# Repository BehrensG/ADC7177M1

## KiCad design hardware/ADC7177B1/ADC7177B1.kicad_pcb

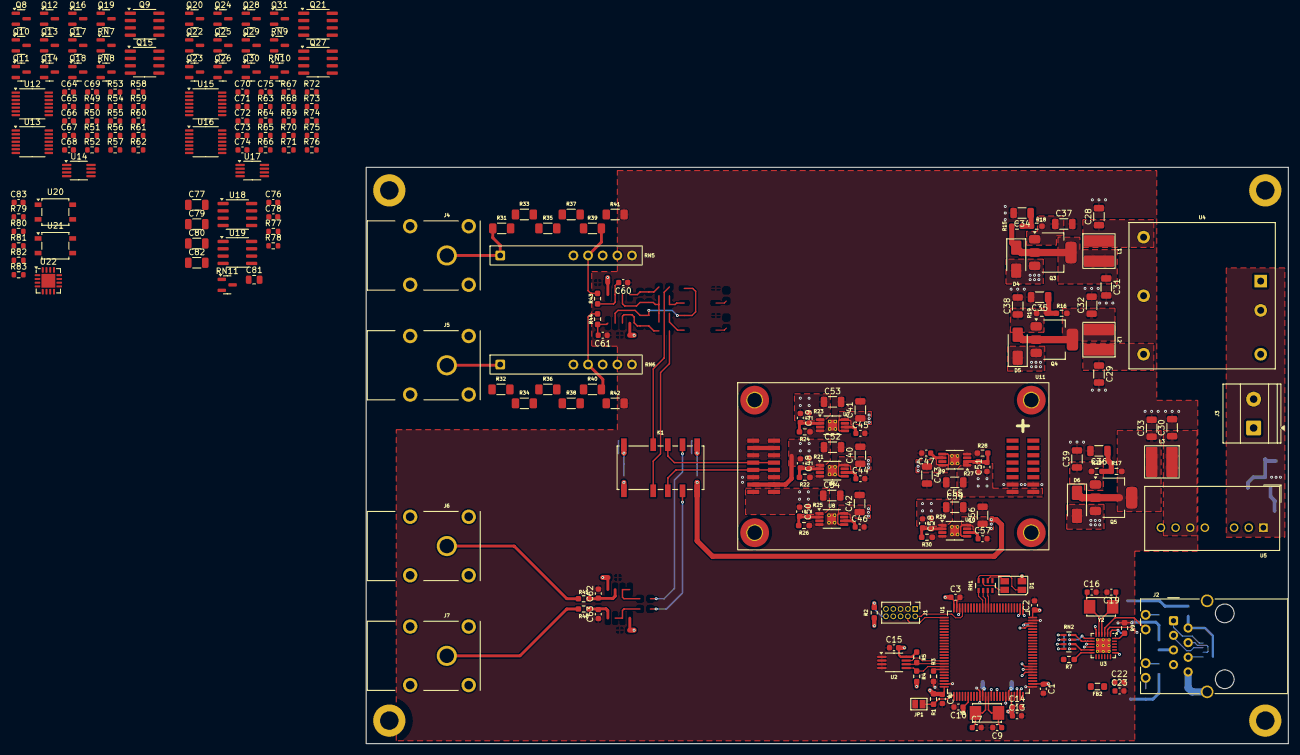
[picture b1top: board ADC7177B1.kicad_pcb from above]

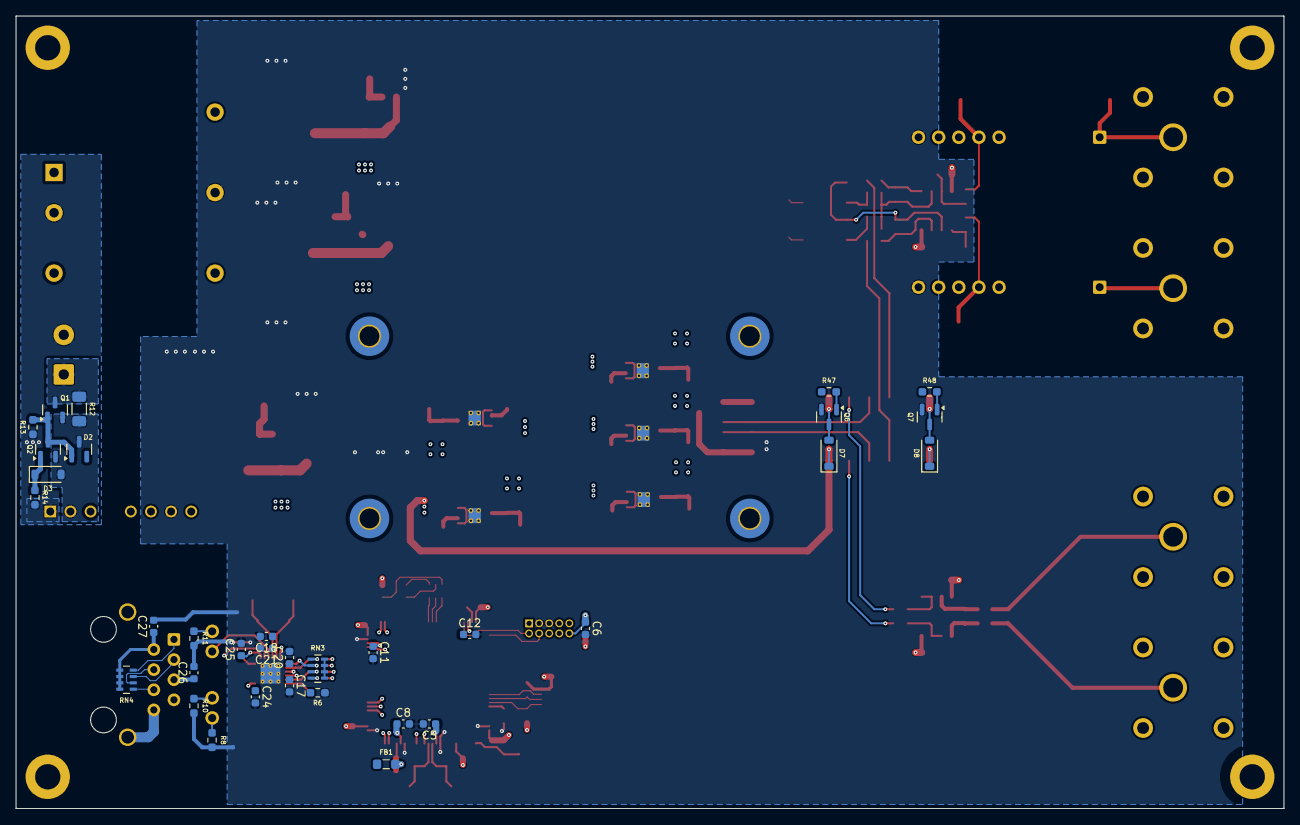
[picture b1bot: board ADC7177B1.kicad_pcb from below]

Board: 4 copper layers, 160.0 x 100.0 mm, 262 parts (33 on the bottom side), 178 nets.

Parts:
C1, C2, C3, C4, C5, C6, C8, C14, C15, C17, C23, C24, C25, C26, C27, C60, C61, C62, C63, C64, C65, C66, C67, C68, C69, C70, C71, C72, C73, C74, C75, C76, C78: 0.1u; C_0603_1608Metric
C7, C9, C16, C19: 8p; C_0603_1608Metric
C10, C20, C21, C22: 1u; C_0603_1608Metric
C11, C12: 2u2; C_0603_1608Metric
C13: 10u; C_0603_1608Metric
C18: 470p; C_0603_1608Metric
C28, C29, C30, C31, C32, C33, C34, C35, C36, C37, C38, C39, C40, C41, C42, C43, C52, C53, C54, C55, C56, C59: 10u/50V; C_1206_3216Metric
C44, C45, C46, C47, C48, C49, C50, C51, C57, C58: 10n; C_0603_1608Metric
C77, C79, C80, C82: 10u; C_1206_3216Metric
C81: 2u2; C_0805_2012Metric
C83: 100p; C_0603_1608Metric
D1: ASMB-MTB1-0B3A2; LED_Avago_PLCC4_3.2x2.8mm_CW
D2: BZX84C10LT1G; SOT-23
D3, D7, D8: 1N4148W; D_SOD-123
D4, D5, D6: SS16; D_SMA
FB1, FB2: 742792031; L_0805_2012Metric_Pad1.05x1.20mm_HandSolder
H1, H2, H3, H4: MountingHole; MountingHole_3.2mm_M3_DIN965_Pad
H5, H6, H7, H8: MountingHole; MountingHole_2.5mm_Pad_TopBottom
J1: 20021111-00010T4LF; PinHeader_2x05_P1.27mm_Vertical
J2: RJ45_Wuerth_7499010121A; RJ45_Wuerth_7499010121A_Horizontal
J3: 1715721; TerminalBlock_Phoenix_MKDS-1,5-2_1x02_P5.00mm_Horizontal
J4, J5, J6, J7: Conn_01x01; S16N-PC
JP1: Open; SolderJumper-2_P1.3mm_Open_Pad1.0x1.5mm
K1: G6SK-2F-DC5; G6SK-2F
L1, L2, L3: 74408943100
Q1: SI5618A; SOT-23
Q2, Q6, Q7: MMBT3904; SOT-23
Q3, Q5: FZT851; SOT-223
Q4: FZT951; SOT-223
Q8, Q10, Q12, Q13, Q14, Q16, Q18, Q19, Q20, Q22, Q24, Q25, Q26, Q28, Q30, Q31: MMBT6429; SOT-23
Q9, Q15, Q21, Q27: JFE2140D; SOIC-8_3.9x4.9mm_P1.27mm
Q11, Q17, Q23, Q29: MMBF4392; SOT-23
R1, R2, R6, R8, R22, R24, R26, R28, R30, R47, R48: 10k; R_0603_1608Metric_Pad0.98x0.95mm_HandSolder
R3: 0; R_0603_1608Metric_Pad0.98x0.95mm_HandSolder
R4, R5: 4k7; R_0603_1608Metric_Pad0.98x0.95mm_HandSolder
R7: 1k5; R_0603_1608Metric_Pad0.98x0.95mm_HandSolder
R9: 12k1; R_0603_1608Metric_Pad0.98x0.95mm_HandSolder
R10, R11: 560; R_0603_1608Metric_Pad0.98x0.95mm_HandSolder
R12: 0; R_1206_3216Metric_Pad1.30x1.75mm_HandSolder
R13, R14: 100k; R_0603_1608Metric_Pad0.98x0.95mm_HandSolder
R15, R16, R17, R18, R19, R20: 1k; R_0603_1608Metric_Pad0.98x0.95mm_HandSolder
R21, R23, R25, R27, R29: 120k; R_0603_1608Metric_Pad0.98x0.95mm_HandSolder
R31, R32, R33, R34, R35, R36, R37, R38: 2M2/0.05%; R_1206_3216Metric_Pad1.30x1.75mm_HandSolder
R39, R40: 1M1/0.05%; R_1206_3216Metric_Pad1.30x1.75mm_HandSolder
R41, R42: 100k/0.05%; R_1206_3216Metric_Pad1.30x1.75mm_HandSolder
R43, R44, R45, R46: 510; R_0603_1608Metric_Pad0.98x0.95mm_HandSolder
R49, R56, R63, R70: 14k7; R_0603_1608Metric
R50, R51, R55, R57, R58, R62, R64, R65, R69, R71, R72, R76: 21k5/0.125W; R_0603_1608Metric
R52, R53, R54, R59, R60, R61, R66, R67, R68, R73, R74, R75: 2k/0.1%; R_0603_1608Metric
R77, R78: 10k/0.01%/2ppm; R_0603_1608Metric
R79, R80: 1k; R_0603_1608Metric
R81: 5k49/0.1%/10ppm; R_0603_1608Metric
R82: 499/0.01%/2ppm; R_0603_1608Metric
R83: 10k; R_0603_1608Metric
RN1: EXB-V8V102JV; R_Array_Concave_4x0603
RN2: EXB-V8V330JV; R_Array_Concave_4x0603
RN3: EXB-V8V103JV; R_Array_Concave_4x0603
RN4: EXB-38V510JV; R_Array_Concave_4x0603
RN5, RN6: 1776-C68xx
RN7, RN8, RN9, RN10: MPMT4001AT1; SOT-23
RN11: MPMT2002AT5; SOT-23
U1: STM32H743VITx; LQFP-100_14x14mm_P0.5mm
U2: 24LC08B-E/MS; MSOP-8_3x3mm_P0.65mm
U3: LAN8742A; VQFN-24-1EP_4x4mm_P0.5mm_EP2.5x2.5mm_ThermalVias
U4: THN 15-2425; THN_15-2425
U5: TEC 3-2419WI; Converter_DCDC_TRACO_TEC3-24xxUI_THT
U6, U8, U9, U10: TPS7A4901DGN; HVSSOP-8-1EP_3x3mm_P0.65mm_EP1.57x1.89mm_ThermalVias
U7: TPS7A3001DGN; HVSSOP-8-1EP_3x3mm_P0.65mm_EP1.57x1.89mm_ThermalVias
U11: ADC7177M1
U12, U13, U15, U16: ADA4077-4ARUZ; TSSOP-14_4.4x5mm_P0.65mm
U14, U17: ADA4077-2ARMZ; MSOP-8_3x3mm_P0.65mm
U18: AD8676xR; SOIC-8_3.9x4.9mm_P1.27mm
U19: MAX6350ESA; SOIC-8_3.9x4.9mm_P1.27mm
U20, U21: AQY212G3HS; SO-4_4.4x4.3mm_P2.54mm
U22: AD8222xCPZ; LFCSP-16-1EP_4x4mm_P0.65mm_EP2.4x2.4mm
Y1: NX5032GA-16; NX5032GA
Y2: NX5032GA-25; NX5032GA

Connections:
+3.3V: C1.1, C2.1, C3.1, C4.1, C5.1, C8.1, C10.1, C15.2, C17.1, C20.1, C58.1, C59.1, D1.4 (A), FB1.2, FB2.2, J1.1, R1.2, R2.1, R4.1, R5.1, R7.1, R29.1, R79.1, R80.1, RN3.5 (R4.2), RN3.6 (R3.2), RN3.7 (R2.2), RN3.8 (R1.2), U1.6 (VBAT), U1.11 (VDD), U1.20 (VREF+), U1.27 (VDD), U1.50 (VDD), U1.75 (VDD), U1.100 (VDD), U2.8 (VCC), U3.9 (VDDIO), U10.1 (OUT)
+5VA: C50.1, C54.1, R25.1, U8.1 (OUT), U11.A1 (+5VA), U11.A2 (+5VA)
+5VD: C51.1, C55.1, C56.1, D7.1 (K), D8.1 (K), K1.1, K1.6, R27.1, U9.1 (OUT), U10.5 (EN), U10.8 (IN), U11.B15 (+5VD), U11.B16 (+5VD)
+10V: R49.1, R56.1, R63.1, R70.1, R78.2, RN11.3, U18.1
+15V: C48.1, C52.1, C64.1, C65.1, C66.1, C70.1, C71.1, C72.1, C76.1, C77.1, C80.1, Q11.1 (D), Q17.1 (D), Q23.1 (D), Q29.1 (D), R21.1, U6.1 (OUT), U11.A3 (+15V), U11.A4 (+15V), U12.4 (V+), U13.4 (V+), U14.8 (V+), U15.4 (V+), U16.4 (V+), U17.8 (V+), U18.8 (V+), U19.2 (IN), U22.5 (Vs+), U22.16 (Vs+)
+24V: D2.3 (K), D3.2 (A), Q1.2 (S), Q2.2 (E), R12.2, U4.1 (+Vin), U5.2 (+Vin)
-15V: C49.1, C53.1, C67.1, C68.1, C69.1, C73.1, C74.1, C75.1, C78.1, C79.1, R23.1, U7.1 (OUT), U11.A13 (-15V), U11.A14 (-15V), U12.11 (V-), U13.11 (V-), U14.4 (V-), U15.11 (V-), U16.11 (V-), U17.4 (V-), U18.4 (V-), U22.8 (Vs-), U22.13 (Vs-)
/Schematic/ADC Module/IN+: K1.9, U11.A9 (IN+), U11.A10 (IN+)
/Schematic/ADC Module/IN-: K1.4, U11.A7 (IN-), U11.A8 (IN-)
/Schematic/Ethernet/ETH_RXN: J2.6 (RD-), RN4.1 (R1.1), U3.22 (RXN)
/Schematic/Ethernet/ETH_RXP: J2.4 (RD+), RN4.2 (R2.1), U3.23 (RXP)
/Schematic/Ethernet/ETH_TXN: J2.3 (TD-), RN4.3 (R3.1), U3.20 (TXN)
/Schematic/Ethernet/ETH_TXP: J2.1 (TD+), RN4.4 (R4.1), U3.21 (TXP)
/Schematic/Ethernet/LED1: J2.10, U3.3 (LED1/REGOFF)
/Schematic/Ethernet/LED2: J2.12, R8.1, U3.2 (LED2/~INTSEL)
/Schematic/Ethernet/MODE0: RN2.8 (R1.2), RN3.1 (R1.1), U3.8 (RXD0/MODE0)
/Schematic/Ethernet/MODE1: RN2.7 (R2.2), RN3.2 (R2.1), U3.7 (RXD1/MODE1)
/Schematic/Ethernet/MODE2: RN2.6 (R3.2), RN3.3 (R3.1), U3.11 (CRS_DV/MODE2)
/Schematic/Ethernet/REFCLK0: RN2.5 (R4.2), RN3.4 (R4.1), U3.14 (~INT/REFCLKO)
/Schematic/Ethernet/REF_CLK: RN2.4 (R4.1), U1.23 (PA1)
/Schematic/Ethernet/RMII_CRS_DV: RN2.3 (R3.1), U1.31 (PA7)
/Schematic/Ethernet/RMII_MDC: U1.16 (PC1), U3.13 (MDC)
/Schematic/Ethernet/RMII_MDIO: R7.2, U1.24 (PA2), U3.12 (MDIO)
/Schematic/Ethernet/RMII_RXD0: RN2.1 (R1.1), U1.32 (PC4)
/Schematic/Ethernet/RMII_RXD1: RN2.2 (R2.1), U1.33 (PC5)
/Schematic/Ethernet/RMII_TXD0: U1.51 (PB12), U3.17 (TXD0)
/Schematic/Ethernet/RMII_TXD1: U1.52 (PB13), U3.18 (TXD1)
/Schematic/Ethernet/RMII_TXEN: U1.47 (PB11), U3.16 (TXEN)
/Schematic/Frontend/Analog Channels A/INA_N: C61.2, Q15.4, R44.2
/Schematic/Frontend/Analog Channels A/INA_P: C60.2, Q9.4, R43.2
/Schematic/Frontend/Analog Channels A/OUTA_N: Q15.8, U13.8, U22.1 (-)
/Schematic/Frontend/Analog Channels A/OUTA_P: Q9.8, U12.8, U22.4 (+)
/Schematic/Frontend/Analog Channels B/INB_N: C63.2, Q27.4, R46.2
/Schematic/Frontend/Analog Channels B/INB_P: C62.2, Q21.4, R45.2
/Schematic/Frontend/Analog Channels B/OUTB_N: K1.5, Q27.8, U16.8
/Schematic/Frontend/Analog Channels B/OUTB_P: K1.8, Q21.8, U15.8
/Schematic/Frontend/Gain/OUT_N: K1.3, U22.6 (Ref), U22.14
/Schematic/Frontend/Gain/OUT_P: K1.10, R83.1, U22.15
/Schematic/MCU/EEPROM_nWP: U1.91 (PB5), U2.7 (WP)
/Schematic/MCU/I2C1_SCL: R5.2, U1.92 (PB6), U2.6 (SCL)
/Schematic/MCU/I2C1_SDA: R4.2, U1.93 (PB7), U2.5 (SDA)
/Schematic/MCU/LED_BLUE: RN1.3 (R3.1), U1.63 (PC6)
/Schematic/MCU/LED_GREEN: RN1.2 (R2.1), U1.64 (PC7)
/Schematic/MCU/LED_RED: RN1.1 (R1.1), U1.65 (PC8)
/Schematic/MCU/MCU_DEF: JP1.1 (A), R1.1, U1.1 (PE2)
/Schematic/MCU/NRST: C6.1, J1.10, R2.2, U1.14 (NRST), U3.15 (~RST)
/Schematic/MCU/TCK_SWCLK: J1.4, U1.76 (PA14)
/Schematic/MCU/TMS_SWDIO: J1.2, U1.72 (PA13)
Earth: J2.8, J2.SH
GND: C1.2, C2.2, C3.2, C4.2, C5.2, C6.2, C7.2, C8.2, C9.2, C10.2, C11.2, C12.2, C13.2, C14.2, C15.1, C16.2, C17.2, C18.2, C19.2, C20.2, C21.2, C22.2, C23.2, C24.2, C25.2, C26.2, C27.2, C28.2, C29.2, C30.2, C31.2, C32.2, C33.2, C34.2, C35.2, C36.2, C37.2, C38.2, C39.2, C40.2, C41.2, C42.2, C43.2, C44.2, C45.2, C46.2, C47.2, C52.2, C53.2, C54.2, C55.2, C56.2, C57.2, C59.2, C60.1, C61.1, C62.1, C63.1, C64.2, C65.2, C66.2, C67.2, C68.2, C69.2, C70.2, C71.2, C72.2, C73.2, C74.2, C75.2, C83.2, J1.3, J1.5, JP1.2 (B), Q6.2 (E), Q7.2 (E), R3.2, R6.1, R8.2, R9.1, R10.2, R11.2, R22.2, R24.2, R26.2, R28.2, R30.2, R41.1, R42.1, RN5.6 (R5), RN6.6 (R5), U1.10 (VSS), U1.19 (VSSA), U1.26 (VSS), U1.49 (VSS), U1.74 (VSS), U1.99 (VSS), U2.1 (A0), U2.2 (A1), U2.3 (A2), U2.4 (GND), U3.25 (VSS), U4.4 (Com), U5.7 (-Vout), U6.4 (GND), U6.9 (EP), U7.4 (GND), U7.9 (EP), U8.4 (GND), U8.9 (EP), U9.4 (GND), U9.9 (EP), U10.4 (GND), U10.9 (EP), U11.A5 (GNDA), U11.A6 (GNDA), U11.A11 (GNDA), U11.A12 (GNDA), U11.A15 (GNDA), U11.A16 (GNDA), U11.B13 (GNDD), U11.B14 (GNDD), U14.3 (+), U14.5 (+), U17.3 (+), U17.5 (+), U22.7 (Ref), U22.9 (+)
GNDA: C76.2, C77.2, C78.2, C79.2, C80.2, C81.2, C82.2, R77.1, RN11.1, U18.5 (+), U19.4 (GND)
GNDS: J3.2, R13.2, R14.2, U4.2 (-Vin), U5.1 (-Vin)
unnamed: C11.1, U1.48 (VCAP)
unnamed: C12.1, U1.73 (VCAP)
unnamed: C34.1, R15.1, R18.1
unnamed: C35.1, R16.1, R19.1
unnamed: C36.1, R17.1, R20.1
unnamed: D1.3 (BK), RN1.6 (R3.2)
unnamed: D1.2 (GK), RN1.7 (R2.2)
unnamed: D1.1 (RK), RN1.8 (R1.2)
unnamed: D2.1 (A), Q1.1 (G), Q2.3 (C), R13.1
unnamed: D3.1 (K), Q2.1 (B), R14.1
unnamed: C40.1, D4.2 (A), Q3.3 (E), U6.5 (EN), U6.8 (IN)
unnamed: C31.1, D4.1 (K), L1.2, Q3.2 (C), Q3.4 (C), R15.2
unnamed: C32.1, D5.2 (A), L2.2, Q4.2 (C), Q4.4 (C), R16.2
unnamed: C41.1, D5.1 (K), Q4.3 (E), U7.5 (EN), U7.8 (IN)
unnamed: C42.1, C43.1, D6.2 (A), Q5.3 (E), U8.5 (EN), U8.8 (IN), U9.5 (EN), U9.8 (IN)
unnamed: C33.1, D6.1 (K), L3.2, Q5.2 (C), Q5.4 (C), R17.2
unnamed: D7.2 (A), K1.7, Q6.3 (C)
unnamed: D8.2 (A), K1.12, Q7.3 (C)
unnamed: J2.9, R11.1
unnamed: J2.11, R10.1
unnamed: J3.1, Q1.3 (D), R12.1
unnamed: J4.1, R31.1, RN5.1 (common)
unnamed: J5.1, R32.1, RN6.1 (common)
unnamed: J6.1, R45.1
unnamed: J7.1, R46.1
unnamed: C37.1, Q3.1 (B), R18.2
unnamed: C38.1, Q4.1 (B), R19.2
unnamed: C39.1, Q5.1 (B), R20.2
unnamed: Q6.1 (B), R47.2
unnamed: Q7.1 (B), R48.2
unnamed: Q8.1 (B), U12.1
unnamed: Q8.2 (E), Q10.1 (B), R50.2
unnamed: Q8.3 (C), Q9.1, Q10.3 (C), U12.10 (+), U12.12 (+)
unnamed: Q10.2 (E), R50.1, R52.1, RN7.3, U12.2 (-)
unnamed: Q11.3 (G), U12.13 (-), U12.14
unnamed: Q9.2, Q9.6, Q11.2 (S)
unnamed: Q12.1 (B), Q13.2 (E), R55.2
unnamed: Q9.5, Q12.3 (C), Q13.3 (C), U12.9 (-)
unnamed: Q12.2 (E), R54.2, R55.1, RN7.1, U12.6 (-)
unnamed: Q13.1 (B), U12.7
unnamed: Q14.1 (B), U13.1
unnamed: Q14.3 (C), Q15.1, Q16.3 (C), U13.10 (+), U13.12 (+)
unnamed: Q14.2 (E), Q16.1 (B), R57.2
unnamed: Q16.2 (E), R57.1, R59.1, RN8.3, U13.2 (-)
unnamed: Q17.3 (G), U13.13 (-), U13.14
unnamed: Q15.2, Q15.6, Q17.2 (S)
unnamed: Q18.1 (B), Q19.2 (E), R62.2
unnamed: Q15.5, Q18.3 (C), Q19.3 (C), U13.9 (-)
unnamed: Q18.2 (E), R61.2, R62.1, RN8.1, U13.6 (-)
unnamed: Q19.1 (B), U13.7
unnamed: Q20.1 (B), U15.1
unnamed: Q20.3 (C), Q21.1, Q22.3 (C), U15.10 (+), U15.12 (+)
unnamed: Q20.2 (E), Q22.1 (B), R64.2
unnamed: Q22.2 (E), R64.1, R66.1, RN9.3, U15.2 (-)
unnamed: Q23.3 (G), U15.13 (-), U15.14
unnamed: Q21.2, Q21.6, Q23.2 (S)
unnamed: Q24.1 (B), Q25.2 (E), R69.2
unnamed: Q21.5, Q24.3 (C), Q25.3 (C), U15.9 (-)
unnamed: Q24.2 (E), R68.2, R69.1, RN9.1, U15.6 (-)
unnamed: Q25.1 (B), U15.7
unnamed: Q26.1 (B), U16.1
unnamed: Q26.3 (C), Q27.1, Q28.3 (C), U16.10 (+), U16.12 (+)
unnamed: Q26.2 (E), Q28.1 (B), R71.2
unnamed: Q28.2 (E), R71.1, R73.1, RN10.3, U16.2 (-)
unnamed: Q29.3 (G), U16.13 (-), U16.14
unnamed: Q27.2, Q27.6, Q29.2 (S)
unnamed: Q30.1 (B), Q31.2 (E), R76.2
unnamed: Q27.5, Q30.3 (C), Q31.3 (C), U16.9 (-)
unnamed: Q30.2 (E), R75.2, R76.1, RN10.1, U16.6 (-)
unnamed: Q31.1 (B), U16.7
unnamed: R31.2, R33.1
unnamed: R32.2, R34.1
unnamed: R33.2, R35.1
unnamed: R34.2, R36.1
unnamed: R35.2, R37.1
unnamed: R36.2, R38.1
unnamed: R37.2, R39.1
unnamed: R38.2, R40.1
unnamed: R52.2, R53.2, R54.1, RN7.2, U14.1
unnamed: R59.2, R60.2, R61.1, RN8.2, U14.7
unnamed: R66.2, R67.2, R68.1, RN9.2, U17.1
unnamed: R73.2, R74.2, R75.1, RN10.2, U17.7
unnamed: R79.2, U20.1
unnamed: R80.2, U21.1
unnamed: R81.1, U20.4
unnamed: R81.2, R82.2, U22.2 (Rg)
unnamed: R82.1, U21.4
unnamed: R39.2, R41.2, R43.1, RN5.3 (R2)
unnamed: R40.2, R42.2, R44.1, RN6.3 (R2)
unnamed: R3.1, U1.94 (BOOT0)
unnamed: C7.1, U1.12 (PH0), Y1.1
unnamed: C9.1, U1.13 (PH1), Y1.2
unnamed: R9.2, U3.24 (RBIAS)
unnamed: R6.2, U3.10 (RXER/PHYAD0)
unnamed: C18.1, C21.1, U3.6 (VDDCR)
unnamed: C16.1, U3.5 (XTAL1/CLKIN), Y2.2
unnamed: C19.1, U3.4 (XTAL2), Y2.1
unnamed: C28.1, L1.1, U4.3 (+Vout)
unnamed: C29.1, L2.1, U4.5 (-Vout)
unnamed: C30.1, L3.1, U5.6 (+Vout)
unnamed: C48.2, R21.2, R22.1, U6.2 (FB)
unnamed: C44.1, U6.6 (NR/SS)
unnamed: C49.2, R23.2, R24.1, U7.2 (FB)
unnamed: C45.1, U7.6 (NR/SS)
unnamed: C50.2, R25.2, R26.1, U8.2 (FB)
unnamed: C46.1, U8.6 (NR/SS)
unnamed: C51.2, R27.2, R28.1, U9.2 (FB)
unnamed: C47.1, U9.6 (NR/SS)
unnamed: C58.2, R29.2, R30.1, U10.2 (FB)
unnamed: C57.1, U10.6 (NR/SS)
unnamed: R51.2, R53.1, U12.3 (+), U12.5 (+)
unnamed: R58.2, R60.1, U13.3 (+), U13.5 (+)
unnamed: R49.2, R51.1, U14.2 (-)
unnamed: R56.2, R58.1, U14.6 (-)
unnamed: R65.2, R67.1, U15.3 (+), U15.5 (+)
unnamed: R72.2, R74.1, U16.3 (+), U16.5 (+)
unnamed: R63.2, R65.1, U17.2 (-)
unnamed: R70.2, R72.1, U17.6 (-)
unnamed: C82.1, U18.3 (+), U19.6 (OUT)
unnamed: R77.2, R78.1, RN11.2, U18.2 (-)
unnamed: U18.6 (-), U18.7
unnamed: C81.1, U19.3 (NR)
unnamed: U20.3, U21.3, U22.3 (Rg)
unnamed: C83.1, R83.2, U22.12 (-)
VCCQ: C22.1, C23.1, C24.1, C25.1, C26.1, C27.1, FB2.1, J2.2 (TCT), J2.5 (RCT), RN4.5 (R4.2), RN4.6 (R3.2), RN4.7 (R2.2), RN4.8 (R1.2), U3.1 (VDD2A), U3.19 (VDD1A)
VDDA: C13.1, C14.1, FB1.1, U1.21 (VDDA)

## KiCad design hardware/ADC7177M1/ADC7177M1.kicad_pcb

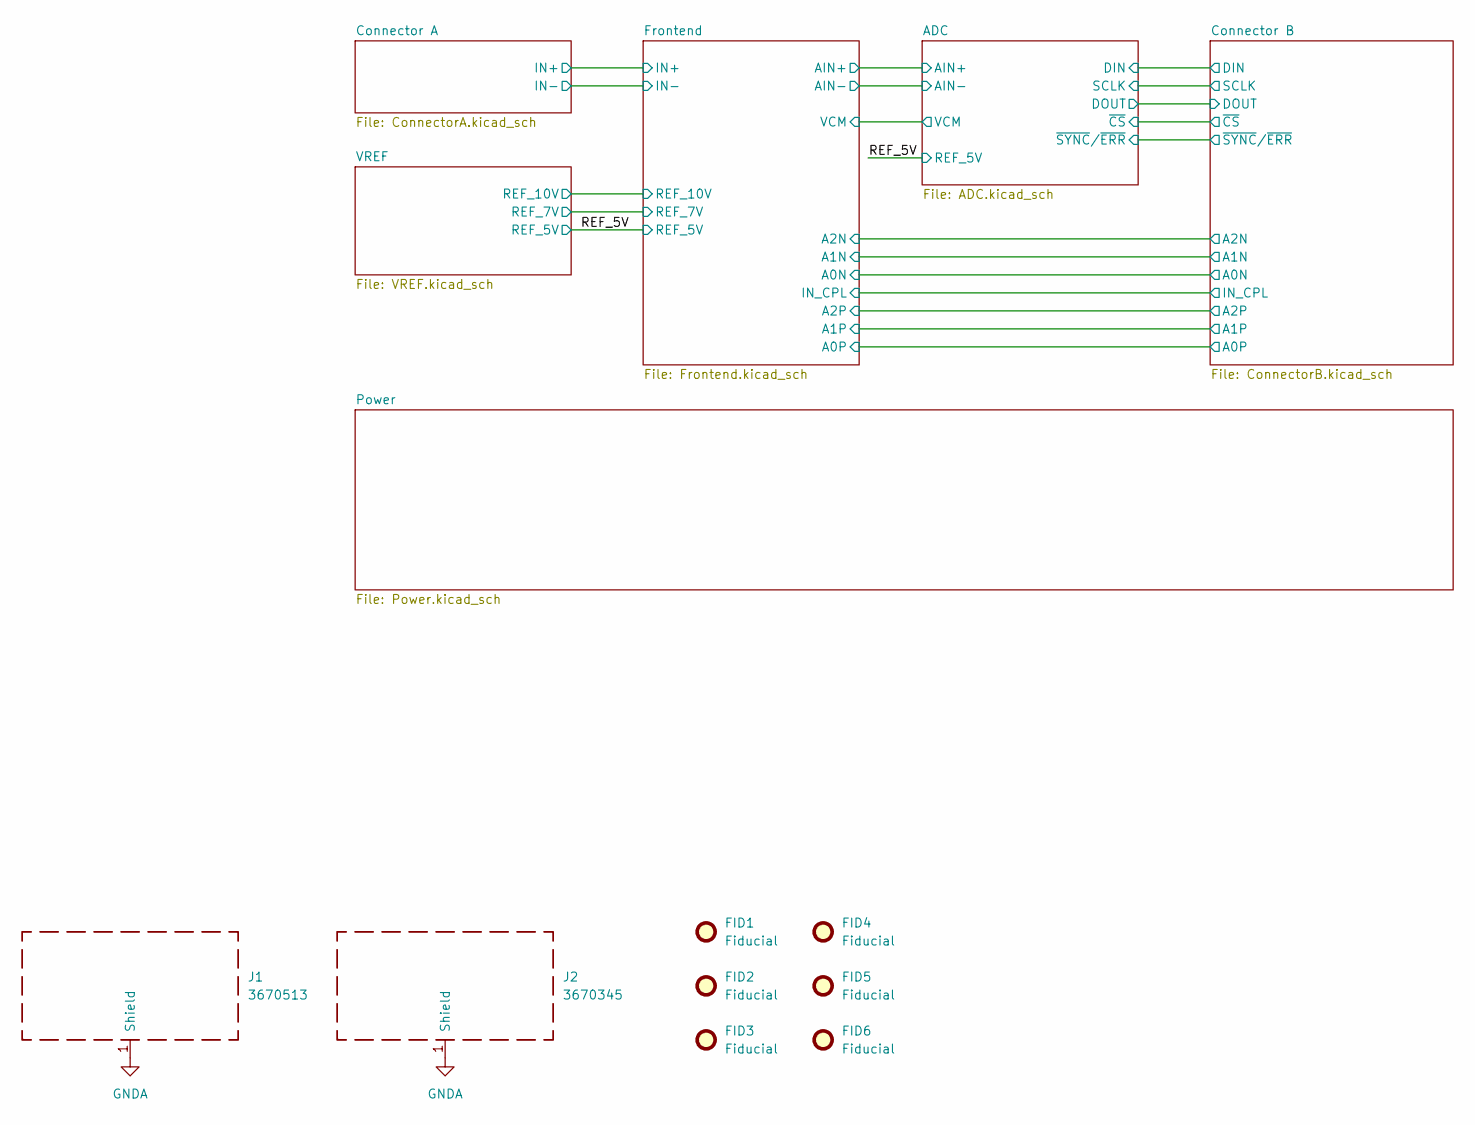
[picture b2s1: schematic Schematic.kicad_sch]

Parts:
FID1, FID2, FID3, FID4, FID5, FID6: Fiducial; Fiducial_0.5mm_Mask1mm
J1: 3670513
J2: 3670345

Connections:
GNDA: J1.1 (Shield), J2.1 (Shield); also elsewhere on the board

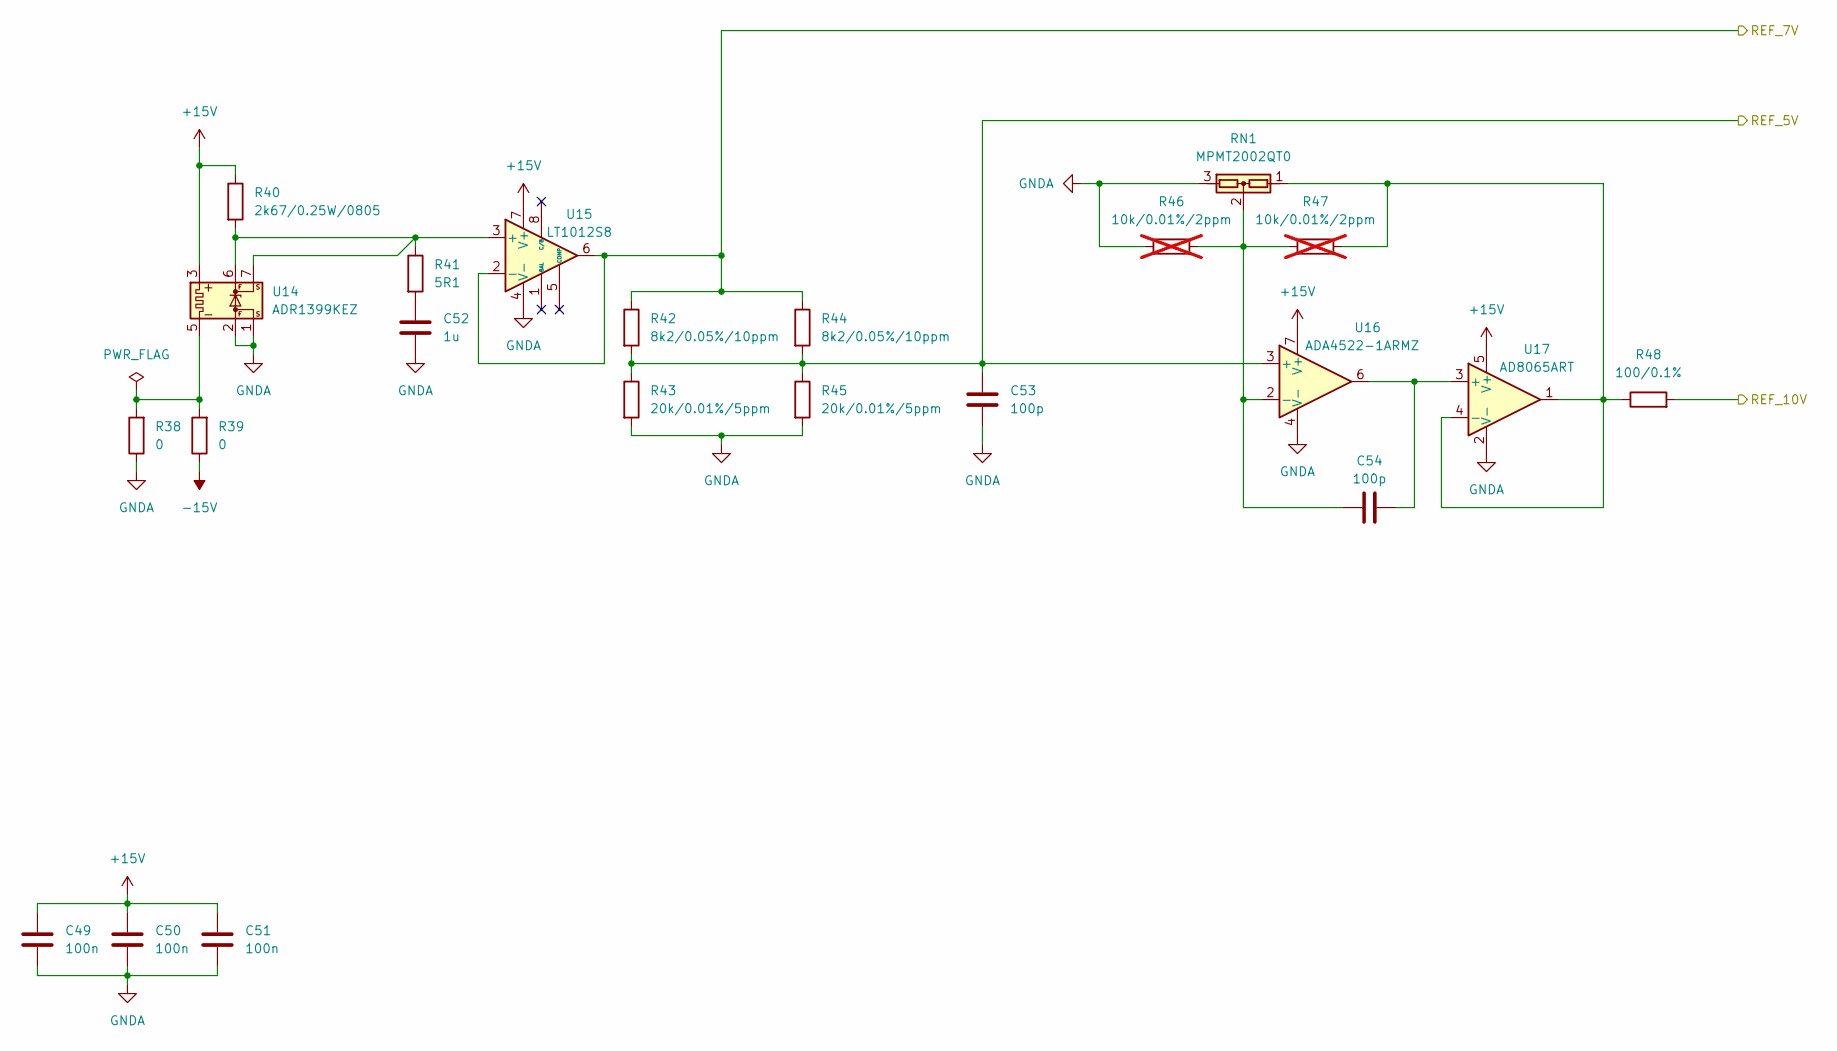
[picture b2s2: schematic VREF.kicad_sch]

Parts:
C49, C50, C51: 100n; C_0603_1608Metric
C52: 1u; C_0603_1608Metric
C53, C54: 100p; C_0603_1608Metric
R38, R39: 0; R_0603_1608Metric
R40: 2k67/0.25W/0805; R_0805_2012Metric
R41: 5R1; R_0603_1608Metric
R42, R44: 8k2/0.05%/10ppm; R_0603_1608Metric
R43, R45: 20k/0.01%/5ppm; R_0603_1608Metric
R46, R47: 10k/0.01%/2ppm; R_0603_1608Metric; not fitted
R48: 100/0.1%; R_0603_1608Metric
RN1: MPMT2002QT0; SOT-23
U14: ADR1399KEZ; Analog_LCC-8_5x5mm_P1.27mm
U15: LT1012S8; SOIC-8_3.9x4.9mm_P1.27mm
U16: ADA4522-1ARMZ; MSOP-8_3x3mm_P0.65mm
U17: AD8065ART; SOT-23-5

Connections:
+15V: C49.1, C50.1, C51.1, R40.1, U14.3 (HEATER+), U15.7 (V+), U16.7 (V+), U17.5 (V+); also elsewhere on the board
-15V: R39.1; also elsewhere on the board
/Schematic/Frontend/REF_7V: R42.1, R44.1, U15.2 (-), U15.6; also elsewhere on the board
/Schematic/Frontend/REF_10V: R48.2; also elsewhere on the board
/Schematic/REF_5V: C53.1, R42.2, R43.1, R44.2, R45.1, U16.3 (+); also elsewhere on the board
GNDA: C49.2, C50.2, C51.2, C52.2, C53.2, R38.1, R43.2, R45.2, R46.1, RN1.3, U14.1 (-REFS), U14.2 (-REFF), U15.4 (V-), U16.4 (V-), U17.2 (V-); also elsewhere on the board
unnamed: C52.1, R41.2
unnamed: R40.2, R41.1, U14.6 (+REFF), U14.7 (+REFS), U15.3 (+)
unnamed: R38.2, R39.2, U14.5 (HEATER-)
unnamed: C54.1, R46.2, R47.1, RN1.2, U16.2 (-)
unnamed: C54.2, U16.6, U17.3 (+)
unnamed: R47.2, R48.1, RN1.1, U17.1, U17.4 (-)

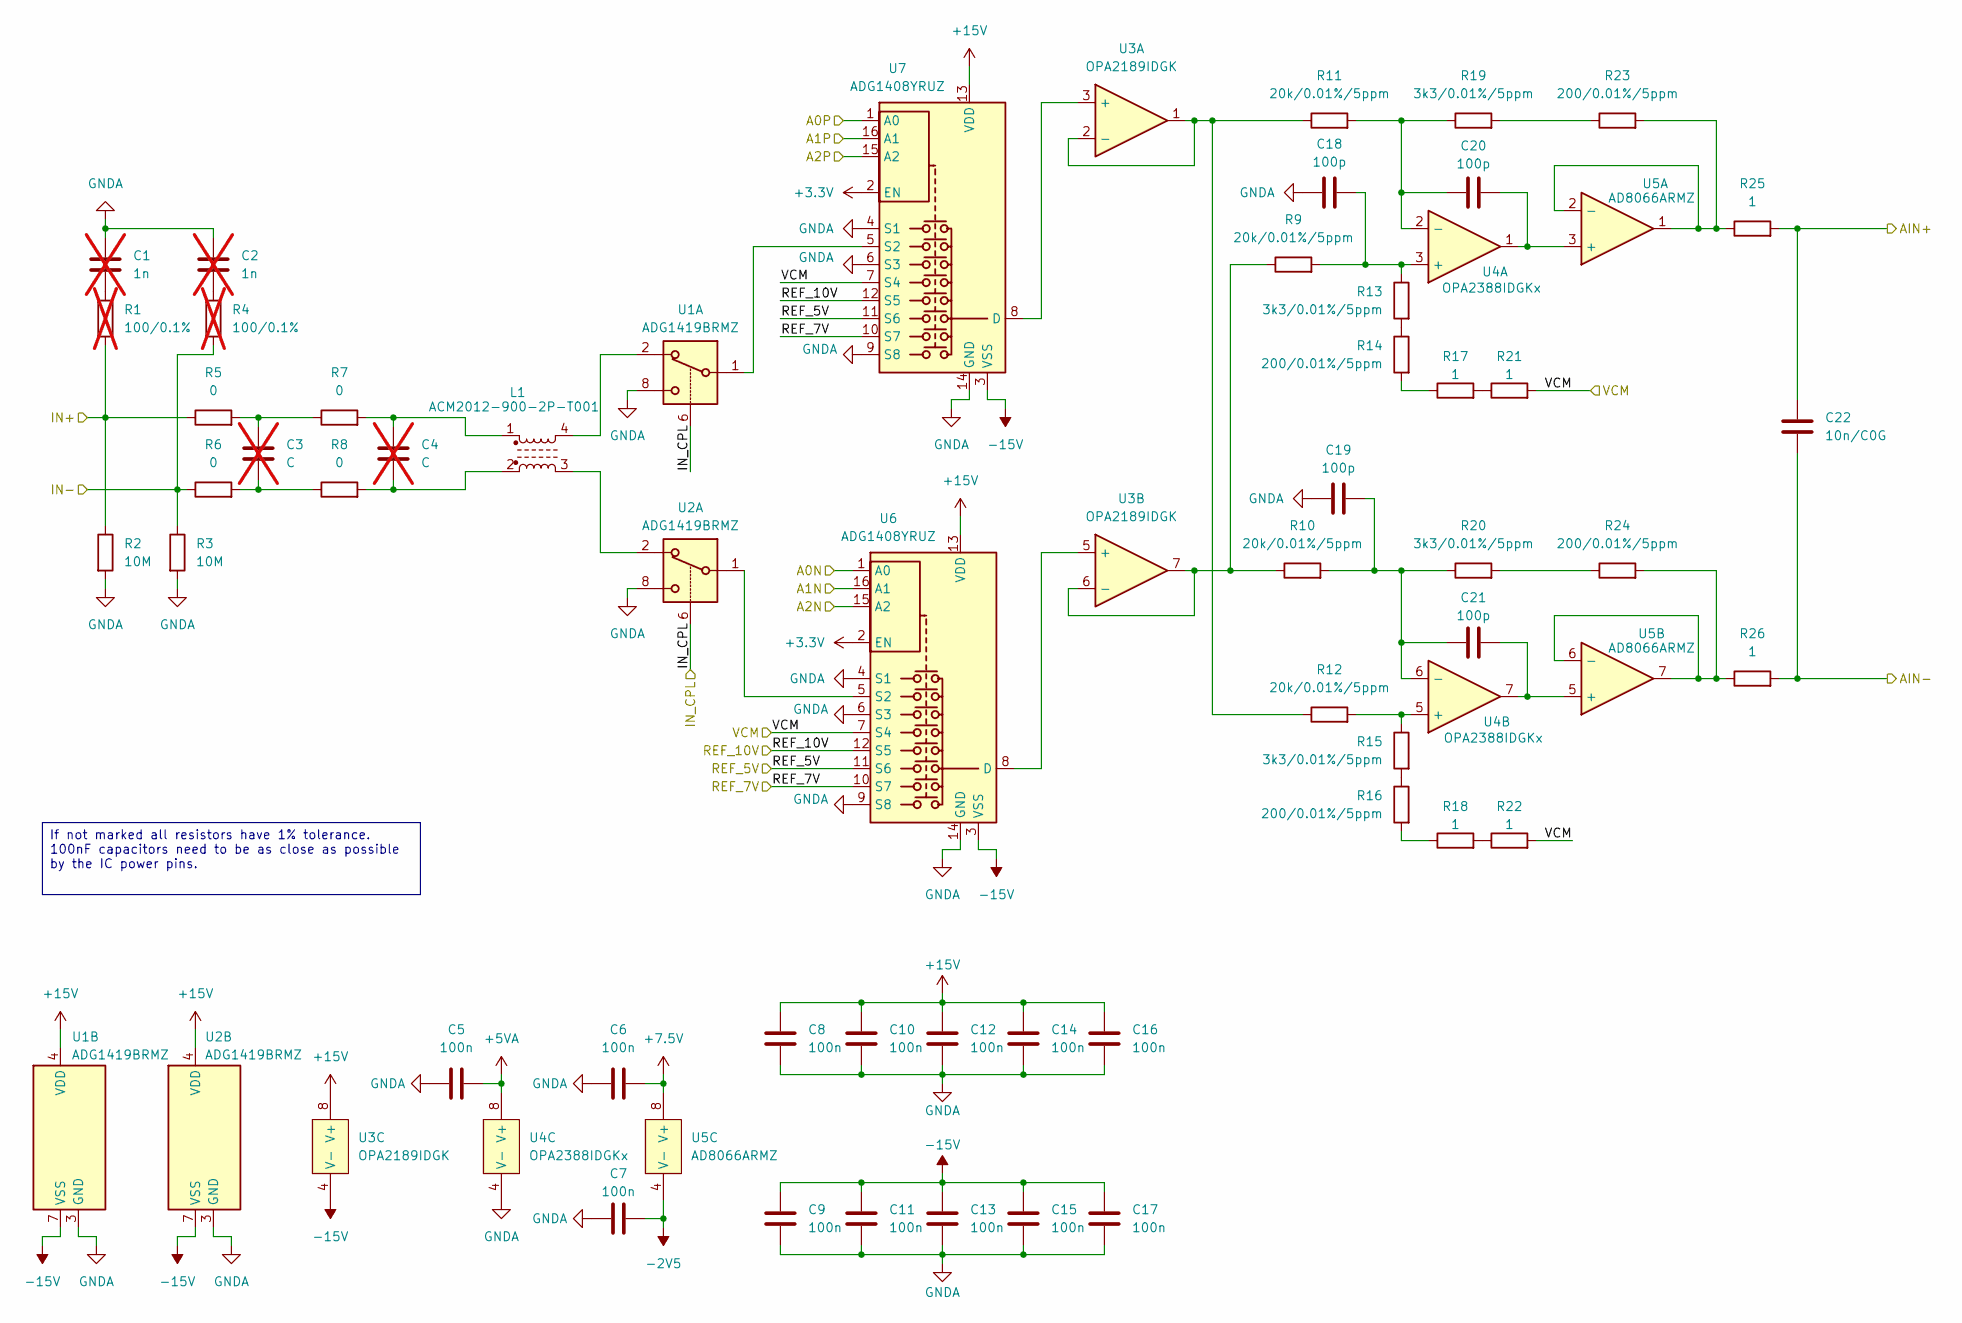
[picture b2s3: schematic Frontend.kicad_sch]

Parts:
C1, C2: 1n; C_0603_1608Metric; not fitted
C3, C4: C; C_0603_1608Metric; not fitted
C5, C6, C7, C8, C9, C10, C11, C12, C13, C14, C15, C16, C17: 100n; C_0603_1608Metric
C18, C19, C20, C21: 100p; C_0603_1608Metric
C22: 10n/C0G; C_0603_1608Metric
L1: ACM2012-900-2P-T001
R1, R4: 100/0.1%; R_0603_1608Metric; not fitted
R2, R3: 10M; R_0603_1608Metric
R5, R6, R7, R8: 0; R_0603_1608Metric
R9, R10, R11, R12: 20k/0.01%/5ppm; R_0603_1608Metric
R13, R15, R19, R20: 3k3/0.01%/5ppm; R_0603_1608Metric
R14, R16, R23, R24: 200/0.01%/5ppm; R_0603_1608Metric
R17, R18, R21, R22, R25, R26: 1; R_0603_1608Metric
U1, U2: ADG1419BRMZ; MSOP-8_3x3mm_P0.65mm
U3: OPA2189IDGK; VSSOP-8_3x3mm_P0.65mm
U4: OPA2388IDGKx; VSSOP-8_3x3mm_P0.65mm
U5: AD8066ARMZ; MSOP-8_3x3mm_P0.65mm
U6, U7: ADG1408YRUZ; TSSOP-16_4.4x5mm_P0.65mm

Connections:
+3.3V: U6.2 (EN), U7.2 (EN); also elsewhere on the board
+5VA: C5.2, U4.8 (V+); also elsewhere on the board
+7.5V: C6.2, U5.8 (V+); also elsewhere on the board
+15V: C8.1, C10.1, C12.1, C14.1, C16.1, U1.4 (VDD), U2.4 (VDD), U3.8 (V+), U6.13 (VDD), U7.13 (VDD); also elsewhere on the board
-2V5: C7.2, U5.4 (V-); also elsewhere on the board
-15V: C9.1, C11.1, C13.1, C15.1, C17.1, U1.7 (VSS), U2.7 (VSS), U3.4 (V-), U6.3 (VSS), U7.3 (VSS); also elsewhere on the board
/Schematic/ADC/AIN+: C22.1, R25.2; also elsewhere on the board
/Schematic/ADC/AIN-: C22.2, R26.2; also elsewhere on the board
/Schematic/ADC/VCM: R21.2, R22.2, U6.7 (S4), U7.7 (S4); also elsewhere on the board
/Schematic/Connector A/IN+: R1.2, R2.1, R5.1; also elsewhere on the board
/Schematic/Connector A/IN-: R3.1, R4.2, R6.1; also elsewhere on the board
/Schematic/Connector B/A0N: U6.1 (A0); also elsewhere on the board
/Schematic/Connector B/A0P: U7.1 (A0); also elsewhere on the board
/Schematic/Connector B/A1N: U6.16 (A1); also elsewhere on the board
/Schematic/Connector B/A1P: U7.16 (A1); also elsewhere on the board
/Schematic/Connector B/A2N: U6.15 (A2); also elsewhere on the board
/Schematic/Connector B/A2P: U7.15 (A2); also elsewhere on the board
/Schematic/Frontend/IN_CPL: U1.6, U2.6; also elsewhere on the board
/Schematic/Frontend/REF_7V: U6.10 (S7), U7.10 (S7); also elsewhere on the board
/Schematic/Frontend/REF_10V: U6.12 (S5), U7.12 (S5); also elsewhere on the board
/Schematic/REF_5V: U6.11 (S6), U7.11 (S6); also elsewhere on the board
GNDA: C1.1, C2.1, C5.1, C6.1, C7.1, C8.2, C9.2, C10.2, C11.2, C12.2, C13.2, C14.2, C15.2, C16.2, C17.2, C18.1, C19.1, R2.2, R3.2, U1.3 (GND), U1.8, U2.3 (GND), U2.8, U4.4 (V-), U6.4 (S1), U6.6 (S3), U6.9 (S8), U6.14 (GND), U7.4 (S1), U7.6 (S3), U7.9 (S8), U7.14 (GND); also elsewhere on the board
unnamed: C1.2, R1.1
unnamed: C2.2, R4.1
unnamed: C3.1, R5.2, R7.1
unnamed: C3.2, R6.2, R8.1
unnamed: C4.1, L1.1, R7.2
unnamed: C4.2, L1.2, R8.2
unnamed: L1.3, U2.2
unnamed: L1.4, U1.2
unnamed: R13.2, R14.1
unnamed: R14.2, R17.1
unnamed: R15.2, R16.1
unnamed: R16.2, R18.1
unnamed: R17.2, R21.1
unnamed: R18.2, R22.1
unnamed: R19.2, R23.1
unnamed: R20.2, R24.1
unnamed: U3.3 (+), U7.8 (D)
unnamed: R11.1, R12.1, U3.1, U3.2 (-)
unnamed: U3.5 (+), U6.8 (D)
unnamed: R9.1, R10.1, U3.6 (-), U3.7
unnamed: C18.2, R9.2, R13.1, U4.3 (+)
unnamed: C20.1, R11.2, R19.1, U4.2 (-)
unnamed: R12.2, R15.1, U4.5 (+)
unnamed: C19.2, C21.1, R10.2, R20.1, U4.6 (-)
unnamed: C20.2, U4.1, U5.3 (+)
unnamed: R23.2, R25.1, U5.1, U5.2 (-)
unnamed: C21.2, U4.7, U5.5 (+)
unnamed: R24.2, R26.1, U5.6 (-), U5.7
unnamed: U2.1, U6.5 (S2)
unnamed: U1.1, U7.5 (S2)

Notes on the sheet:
If not marked all resistors have 1% tolerance. 100nF capacitors need to be as close as possible by the IC power pins.

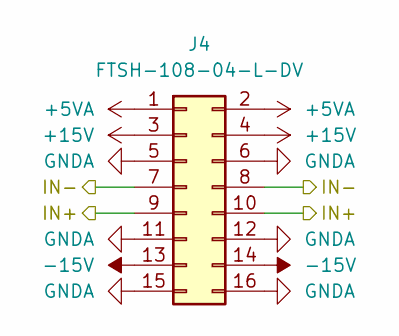
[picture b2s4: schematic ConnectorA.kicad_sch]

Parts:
J4: FTSH-108-04-L-DV; PinHeader_2x08_P1.27mm_Vertical_SMD

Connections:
+5VA: J4.1, J4.2; also elsewhere on the board
+15V: J4.3, J4.4; also elsewhere on the board
-15V: J4.13, J4.14; also elsewhere on the board
/Schematic/Connector A/IN+: J4.9, J4.10; also elsewhere on the board
/Schematic/Connector A/IN-: J4.7, J4.8; also elsewhere on the board
GNDA: J4.5, J4.6, J4.11, J4.12, J4.15, J4.16; also elsewhere on the board
